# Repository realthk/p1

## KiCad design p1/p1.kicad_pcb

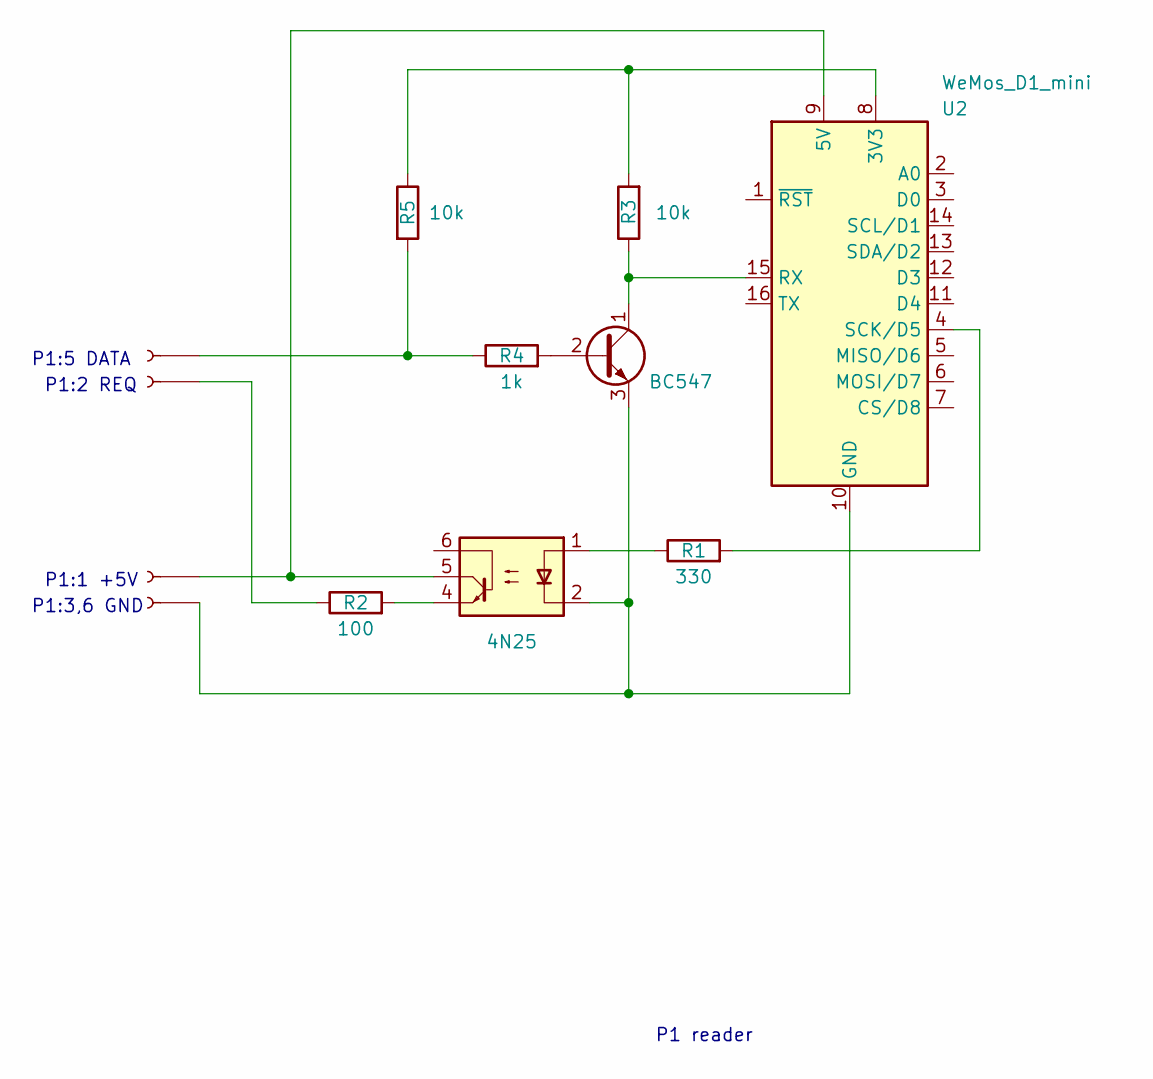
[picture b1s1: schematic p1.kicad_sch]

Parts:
J1, J2: Conn_01x02_Socket; JST_EH_B2B-EH-A_1x02_P2.50mm_Vertical
Q1: BC547; TO-92_Inline
R1: 330; R_Axial_DIN0207_L6.3mm_D2.5mm_P10.16mm_Horizontal
R2: 100; R_Axial_DIN0207_L6.3mm_D2.5mm_P10.16mm_Horizontal
R3, R5: 10k; R_Axial_DIN0207_L6.3mm_D2.5mm_P10.16mm_Horizontal
R4: 1k; R_Axial_DIN0207_L6.3mm_D2.5mm_P10.16mm_Horizontal
U1: 4N25; DIP-6_W7.62mm
U2: WeMos_D1_mini; WEMOS_D1_mini_light

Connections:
unnamed: J1.1, U1.5, U2.9 (5V)
unnamed: J1.2, Q1.3 (E), U1.2, U2.10 (GND)
unnamed: J2.1, R4.1, R5.2
unnamed: J2.2, R2.1
unnamed: Q1.2 (B), R4.2
unnamed: Q1.1 (C), R3.1, U2.15 (RX)
unnamed: R1.1, U1.1
unnamed: R2.2, U1.4
unnamed: R3.2, R5.1, U2.8 (3V3)
unnamed: R1.2, U2.4 (SCK/D5)

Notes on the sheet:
P1 reader
P1:1 +5V
P1:2 REQ
P1:5 DATA
P1:3,6 GND

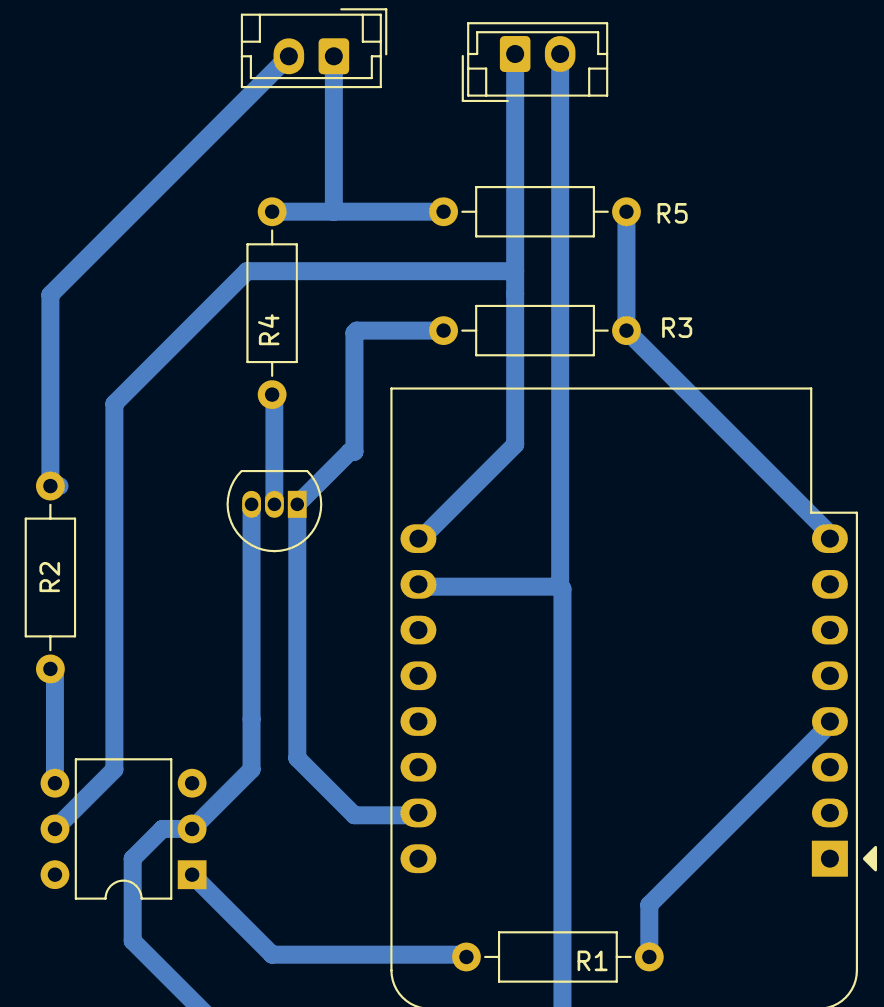
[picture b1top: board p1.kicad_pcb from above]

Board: 2 copper layers, 10 parts (0 on the bottom side), 10 nets.

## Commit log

2025-01-18 előjel fix
2025-01-18 config
2025-05-25 energy_returned
